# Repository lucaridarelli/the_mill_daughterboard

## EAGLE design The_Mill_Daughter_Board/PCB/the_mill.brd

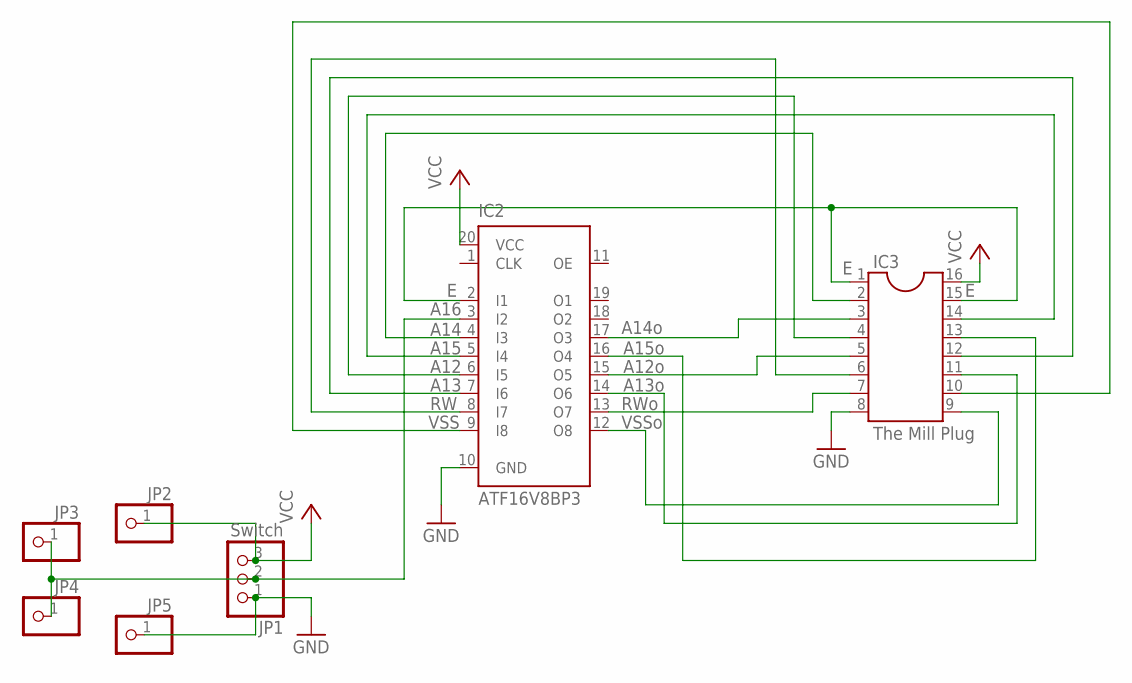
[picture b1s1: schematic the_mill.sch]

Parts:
IC2: ATF16V8BP3; DIL20
IC3: The Mill Plug; DIL16
JP1: Switch; 1X03
JP2, JP3, JP4, JP5: PINHD-1X1; 1X01

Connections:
GND: IC2.10 (GND), IC3.8, JP1.1, JP5.1
unnamed: IC2.4 (I3), IC3.2
unnamed: IC2.5 (I4), IC3.14
unnamed: IC2.2 (I1), IC3.1, IC3.15
unnamed: IC2.6 (I5), IC3.4
unnamed: IC2.7 (I6), IC3.12
unnamed: IC2.3 (I2), JP1.2, JP3.1, JP4.1
unnamed: IC2.8 (I7), IC3.6
unnamed: IC2.9 (I8), IC3.10
unnamed: IC2.12 (O8), IC3.9
unnamed: IC2.13 (O7), IC3.7
unnamed: IC2.14 (O6), IC3.11
unnamed: IC2.15 (O5), IC3.5
unnamed: IC2.16 (O4), IC3.13
unnamed: IC2.17 (O3), IC3.3
VCC: IC2.20 (VCC), IC3.16, JP1.3, JP2.1

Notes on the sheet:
A14o
A15o
A12o
A13o
RWo
VSSo
VSS
A13
A12
A15
A14
A16

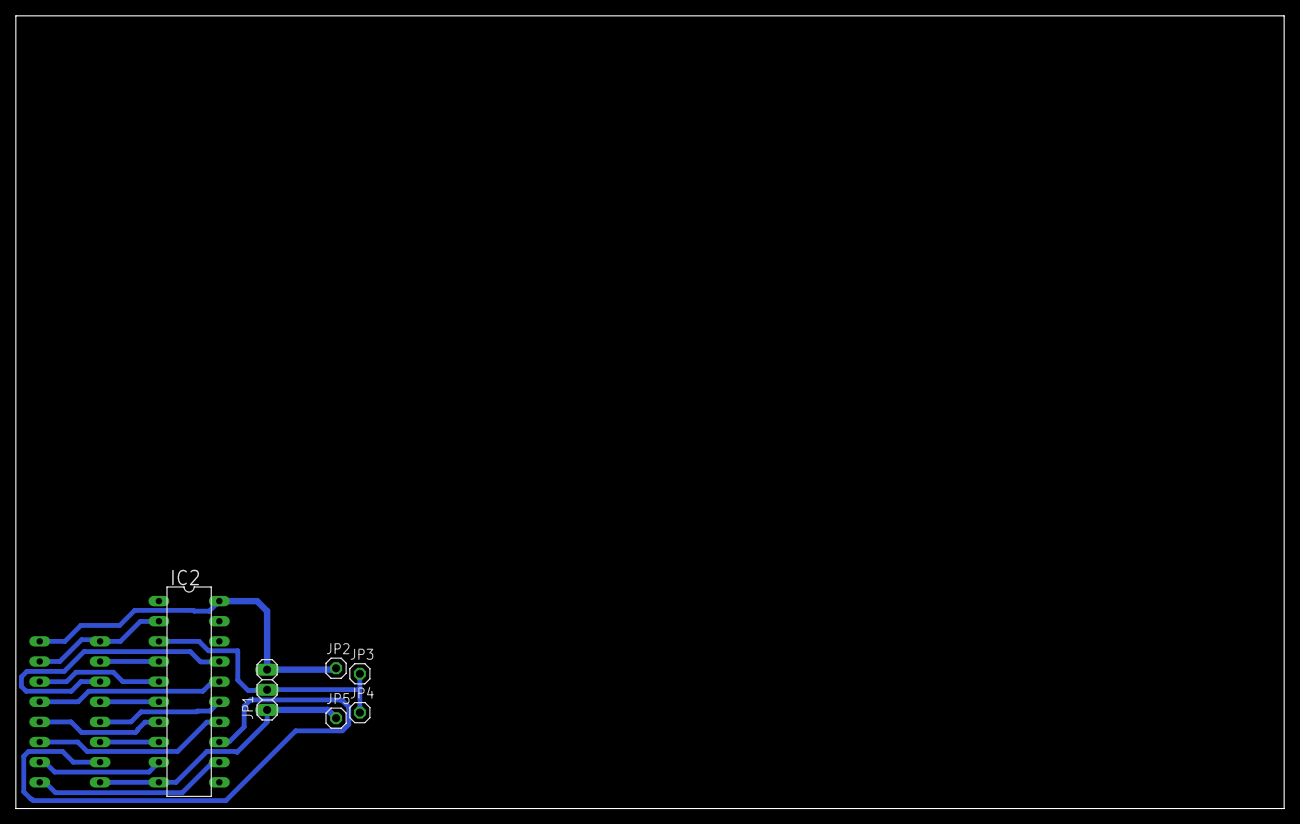
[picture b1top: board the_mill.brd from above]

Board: 2 copper layers, 160.0 x 100.0 mm, 7 parts (1 on the bottom side), 16 nets.

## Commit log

2017-01-16 Second Commit
2017-01-16 Third Commit
2017-01-16 README commit
2017-01-16 Added LICENSE
2017-01-16 License Update
2017-01-16 Readme Update
2017-01-16 Added Pictures
